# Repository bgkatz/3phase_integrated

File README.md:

# 3phase_integrated
3-phase motor controller with integrated position sensor
Firmware here:
https://os.mbed.com/users/benkatz/code/Hobbyking_Cheetah_Compact/

Firmware for new versions with DRV8323:
https://os.mbed.com/users/benkatz/code/HKC_MiniCheetah/

Documentation for using the motor drive:
https://docs.google.com/document/d/1dzNVzblz6mqB3eZVEMyi2MtSngALHdgpTaDJIW_BpS4/edit?usp=sharing

New non-mbed firmware:
https://github.com/bgkatz/motorcontrol

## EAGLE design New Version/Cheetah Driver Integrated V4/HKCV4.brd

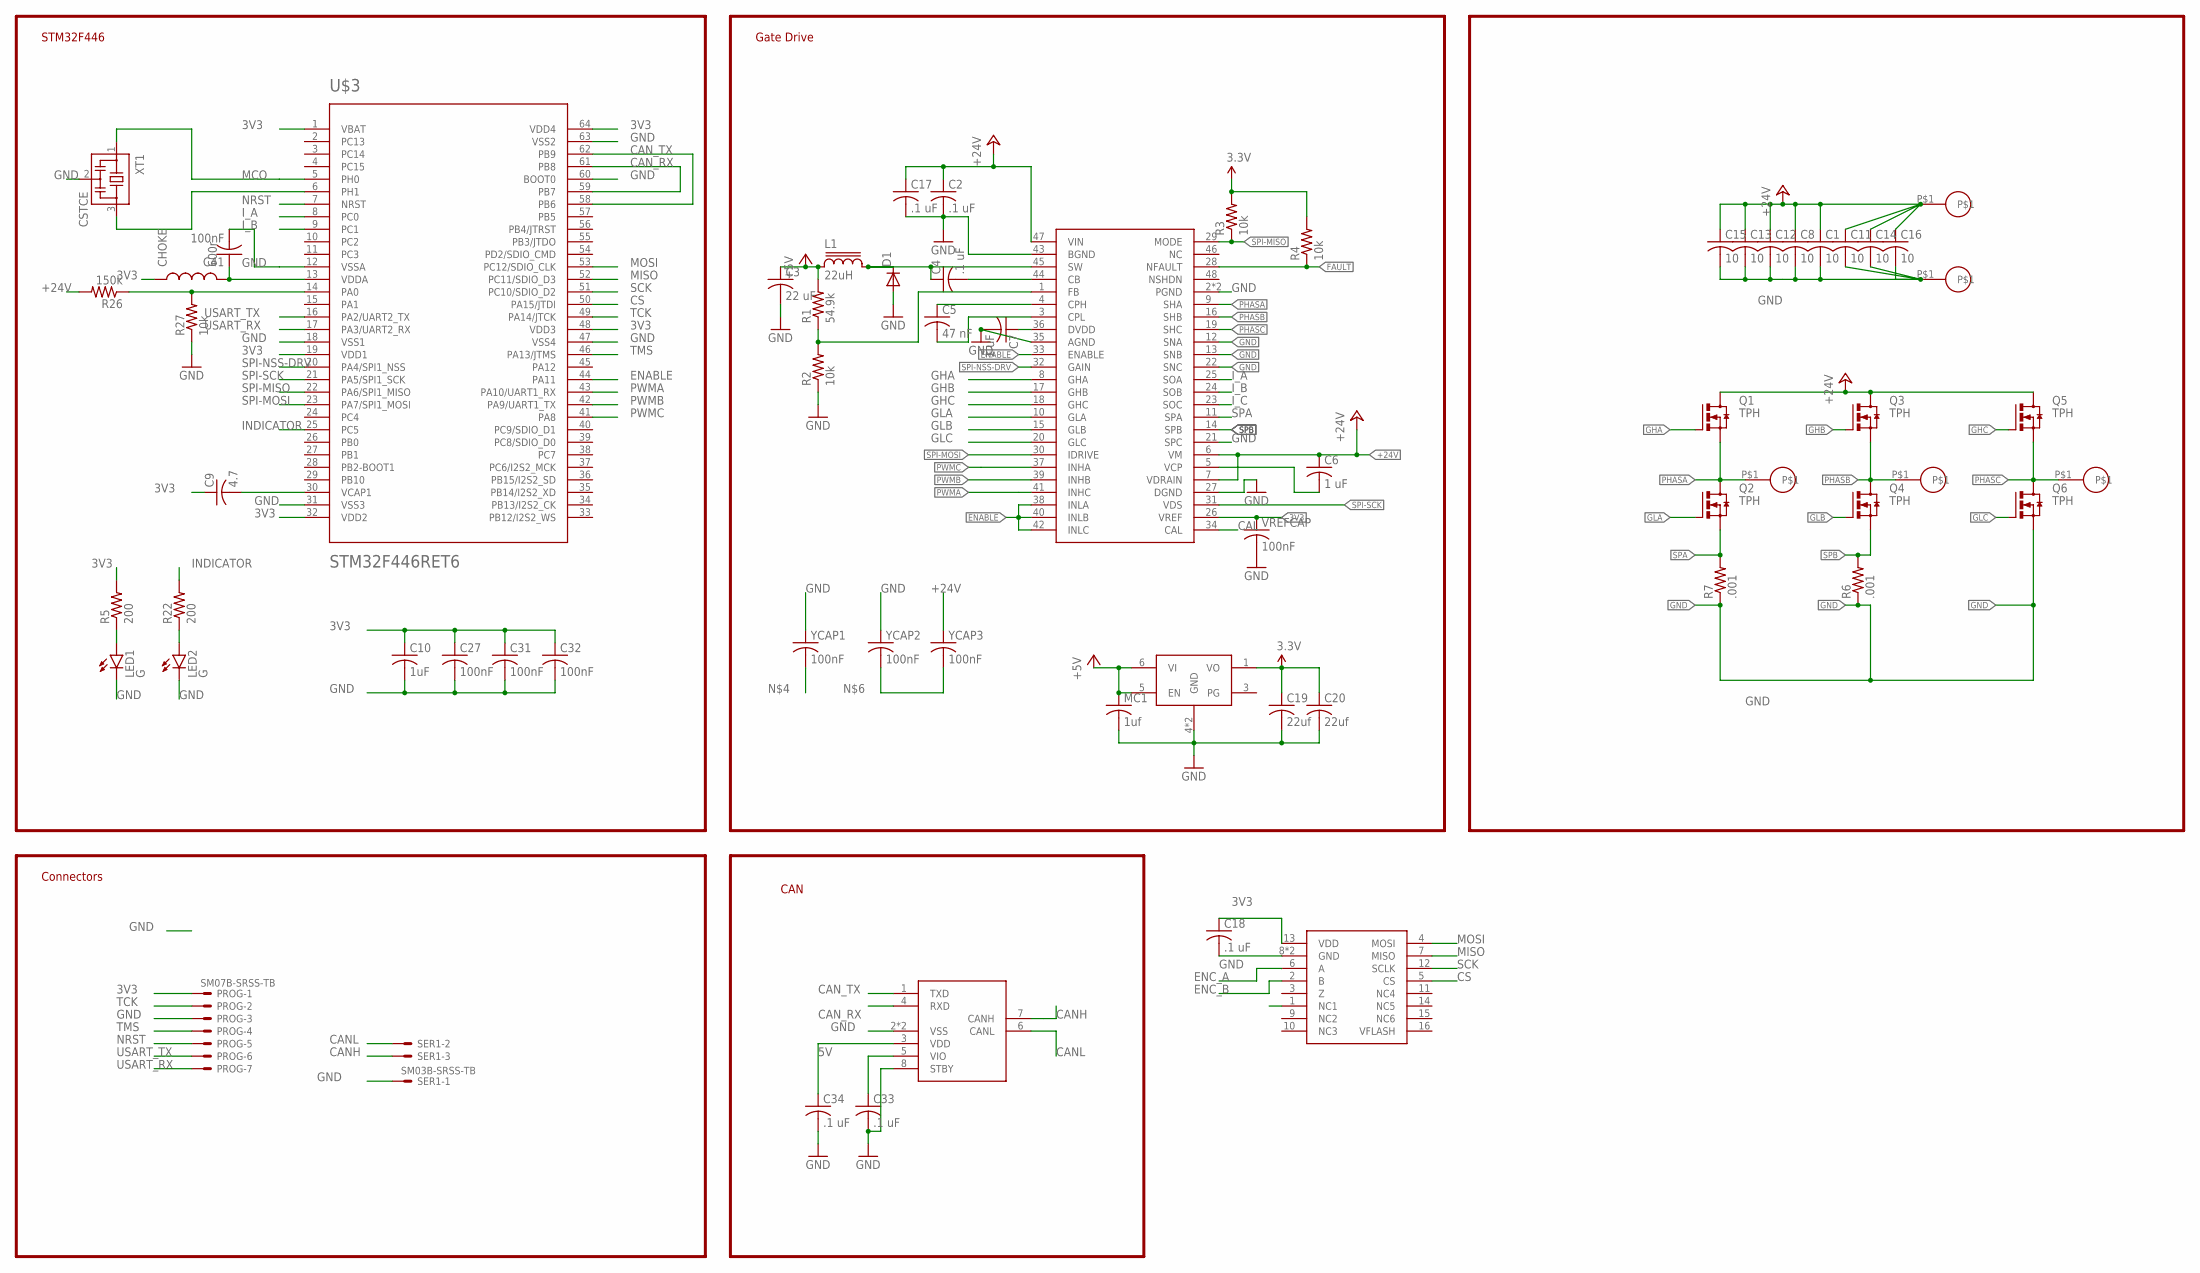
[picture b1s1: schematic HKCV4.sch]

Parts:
C1, C8, C11, C12, C13, C14, C15, C16: 10; C1206K
C2, C4: .1 uF; C0603K
C3: 22 uF; C0603K
C5: 47 nF; C0402K
C6: 1 uF; C0603K
C7: 1 uF; C0402K
C9: 4.7; C0402K
C10: 1uF; C0402K
C17: .1 uF; C1206K
C18, C33, C34: .1 uF; C0402K
C19, C20: 22uf; C0603K
C27, C31, C32: 100nF; C0402K
C41: 100nF; C0402
CHOKE: 600r; 0603
D1: DIODE-SOD123; SOD123
L1: 22uH; SDR0302
LED1, LED2: G; LED-0603
MC1: 1uf; C0402
PROG: SM07B-SRSS-TB
Q1, Q2, Q3, Q4, Q5, Q6: TPH; TRANS_TPH5900CNH,L1Q
R1: 54.9k; R0402
R2, R3, R4, R27: 10k; R0402
R5, R22: 200; R0402
R6, R7: .001; R1210
R26: 150k; R0402
SER1: SM03B-SRSS-TB
U$1: DRV8323RH; QFN50P700X700X90-49N
U$2, U$4, U$5, U$8, U$10: 18_AWG_PAD
U$3: STM32F446RET6; TQFP64
U$6: MCP2542; TDFN
U$7: LDFM; DFN6-3X3
U$11: MA700; QFN16
VREFCAP: 100nF; C0402K
XT1: CSTCE
YCAP1, YCAP2, YCAP3: 100nF; C0402K

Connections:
3V3: C9.1, C10.1, C18.1, C19.1, C20.1, C27.1, C31.1, C32.1, C33.1, CHOKE.1, PROG.1, R3.2, R4.2, R5.2, U$1.26 (VREF), U$3.1 (VBAT), U$3.19 (VDD1), U$3.32 (VDD2), U$3.48 (VDD3), U$3.64 (VDD4), U$6.5 (VIO), U$7.1 (VO), U$11.13 (VDD), VREFCAP.1
5V: C3.1, C34.1, L1.1, MC1.1, R1.2, U$6.3 (VDD), U$7.5 (EN), U$7.6 (VI)
+24V: C1.1, C2.1, C6.1, C8.1, C11.1, C12.1, C13.1, C14.1, C15.1, C16.1, C17.1, Q1.5 (D), Q1.6 (D), Q1.7 (D), Q1.8 (D), Q1.EP (D), Q3.5 (D), Q3.6 (D), Q3.7 (D), Q3.8 (D), Q3.EP (D), Q5.5 (D), Q5.6 (D), Q5.7 (D), Q5.8 (D), Q5.EP (D), R26.2, U$1.6 (VM), U$1.7 (VDRAIN), U$1.47 (VIN), U$8.P$1, YCAP3.1
BOOT: C4.2, U$1.44 (CB)
CAL: U$1.34 (CAL)
CANH: SER1.3, U$6.7 (CANH)
CANL: SER1.2, U$6.6 (CANL)
CAN_RX: U$3.59 (PB7), U$3.61 (PB8), U$6.4 (RXD)
CAN_TX: U$3.58 (PB6), U$3.62 (PB9), U$6.1 (TXD)
CPH: C5.1, U$1.4 (CPH)
CPL: C5.2, U$1.3 (CPL)
CS: U$3.50 (PA15/JTDI), U$11.5 (CS)
DEVICE3.3: C7.1, U$1.36 (DVDD)
ENABLE: U$1.33 (ENABLE), U$1.38 (INLA), U$1.40 (INLB), U$1.42 (INLC), U$3.44 (PA11)
ENC_A: U$11.6 (A)
ENC_B: U$11.2 (B)
FAULT: R4.1, U$1.28 (NFAULT)
FB: R1.1, R2.2, U$1.1 (FB)
GHA: Q1.4 (G), U$1.8 (GHA)
GHB: Q3.4 (G), U$1.17 (GHB)
GHC: Q5.4 (G), U$1.18 (GHC)
GLA: Q2.4 (G), U$1.10 (GLA)
GLB: Q4.4 (G), U$1.15 (GLB)
GLC: Q6.4 (G), U$1.20 (GLC)
GND: C1.2, C2.2, C3.2, C7.2, C8.2, C10.2, C11.2, C12.2, C13.2, C14.2, C15.2, C16.2, C17.2, C18.2, C19.2, C20.2, C27.2, C31.2, C32.2, C33.2, C34.2, C41.2, D1.A, LED1.C, LED2.C, MC1.2, PROG.3, Q6.1 (S), Q6.2 (S), Q6.3 (S), R2.1, R6.1, R7.1, R27.1, SER1.1, U$1.2 (PGND), U$1.12 (SNA), U$1.13 (SNB), U$1.21 (SPC), U$1.22 (SNC), U$1.27 (DGND), U$1.35 (AGND), U$1.43 (BGND), U$1.49 (PGND), U$3.12 (VSSA), U$3.18 (VSS1), U$3.31 (VSS3), U$3.47 (VSS4), U$3.60 (BOOT0), U$3.63 (VSS2), U$6.2 (VSS), U$6.8 (STBY), U$6.9 (VSS), U$7.4 (GND), U$7.EXP (GND), U$10.P$1, U$11.8 (GND), U$11.TH (GND), VREFCAP.2, XT1.2, YCAP1.1, YCAP2.1
INDICATOR: R22.2, U$3.25 (PC5)
I_A: U$1.25 (SOA), U$3.8 (PC0)
I_B: U$1.24 (SOB), U$3.9 (PC1)
I_C: U$1.23 (SOC)
MCO: U$3.5 (PH0), XT1.1
MISO: U$3.52 (PC11/SDIO_D3), U$11.7 (MISO)
MOSI: U$3.53 (PC12/SDIO_CLK), U$11.4 (MOSI)
unnamed: LED1.A, R5.1
unnamed: C41.1, CHOKE.2, U$3.13 (VDDA)
unnamed: C9.2, U$3.30 (VCAP1)
unnamed: YCAP2.2, YCAP3.2
unnamed: R26.1, R27.2, U$3.14 (PA0)
unnamed: LED2.A, R22.1
unnamed: U$3.6 (PH1), XT1.3
NRST: PROG.5, U$3.7 (NRST)
PHASA: Q1.1 (S), Q1.2 (S), Q1.3 (S), Q2.5 (D), Q2.6 (D), Q2.7 (D), Q2.8 (D), Q2.EP (D), U$1.9 (SHA), U$4.P$1
PHASB: Q3.1 (S), Q3.2 (S), Q3.3 (S), Q4.5 (D), Q4.6 (D), Q4.7 (D), Q4.8 (D), Q4.EP (D), U$1.16 (SHB), U$2.P$1
PHASC: Q5.1 (S), Q5.2 (S), Q5.3 (S), Q6.5 (D), Q6.6 (D), Q6.7 (D), Q6.8 (D), Q6.EP (D), U$1.19 (SHC), U$5.P$1
PWMA: U$1.41 (INHC), U$3.43 (PA10/UART1_RX)
PWMB: U$1.39 (INHB), U$3.42 (PA9/UART1_TX)
PWMC: U$1.37 (INHA), U$3.41 (PA8)
SCK: U$3.51 (PC10/SDIO_D2), U$11.12 (SCLK)
SPA: Q2.1 (S), Q2.2 (S), Q2.3 (S), R7.2, U$1.11 (SPA)
SPB: Q4.1 (S), Q4.2 (S), Q4.3 (S), R6.2, U$1.14 (SPB)
SPI-MISO: R3.1, U$1.29 (MODE), U$3.22 (PA6/SPI1_MISO)
SPI-MOSI: U$1.30 (IDRIVE), U$3.23 (PA7/SPI1_MOSI)
SPI-NSS-DRV: U$1.32 (GAIN), U$3.20 (PA4/SPI1_NSS)
SPI-SCK: U$1.31 (VDS), U$3.21 (PA5/SPI1_SCK)
SW: C4.1, D1.C, L1.2, U$1.45 (SW)
TCK: PROG.2, U$3.49 (PA14/JTCK)
TMS: PROG.4, U$3.46 (PA13/JTMS)
USART_RX: PROG.7, U$3.17 (PA3/UART2_RX)
USART_TX: PROG.6, U$3.16 (PA2/UART2_TX)
VCP: C6.2, U$1.5 (VCP)

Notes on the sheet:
Gate Drive
STM32F446
CAN
Connectors

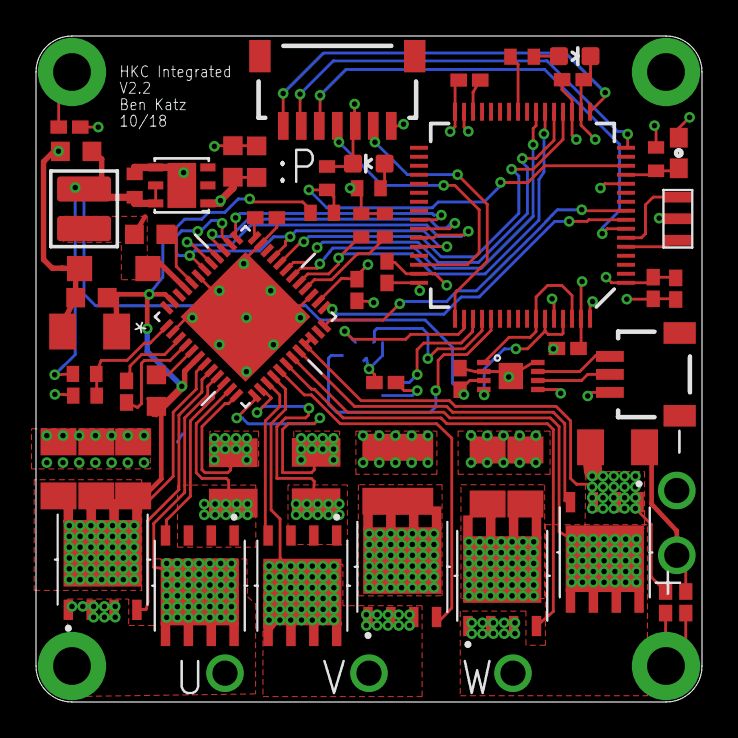
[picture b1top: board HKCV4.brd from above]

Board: 4 copper layers, 37.0 x 37.0 mm, 65 parts (1 on the bottom side), 55 nets.

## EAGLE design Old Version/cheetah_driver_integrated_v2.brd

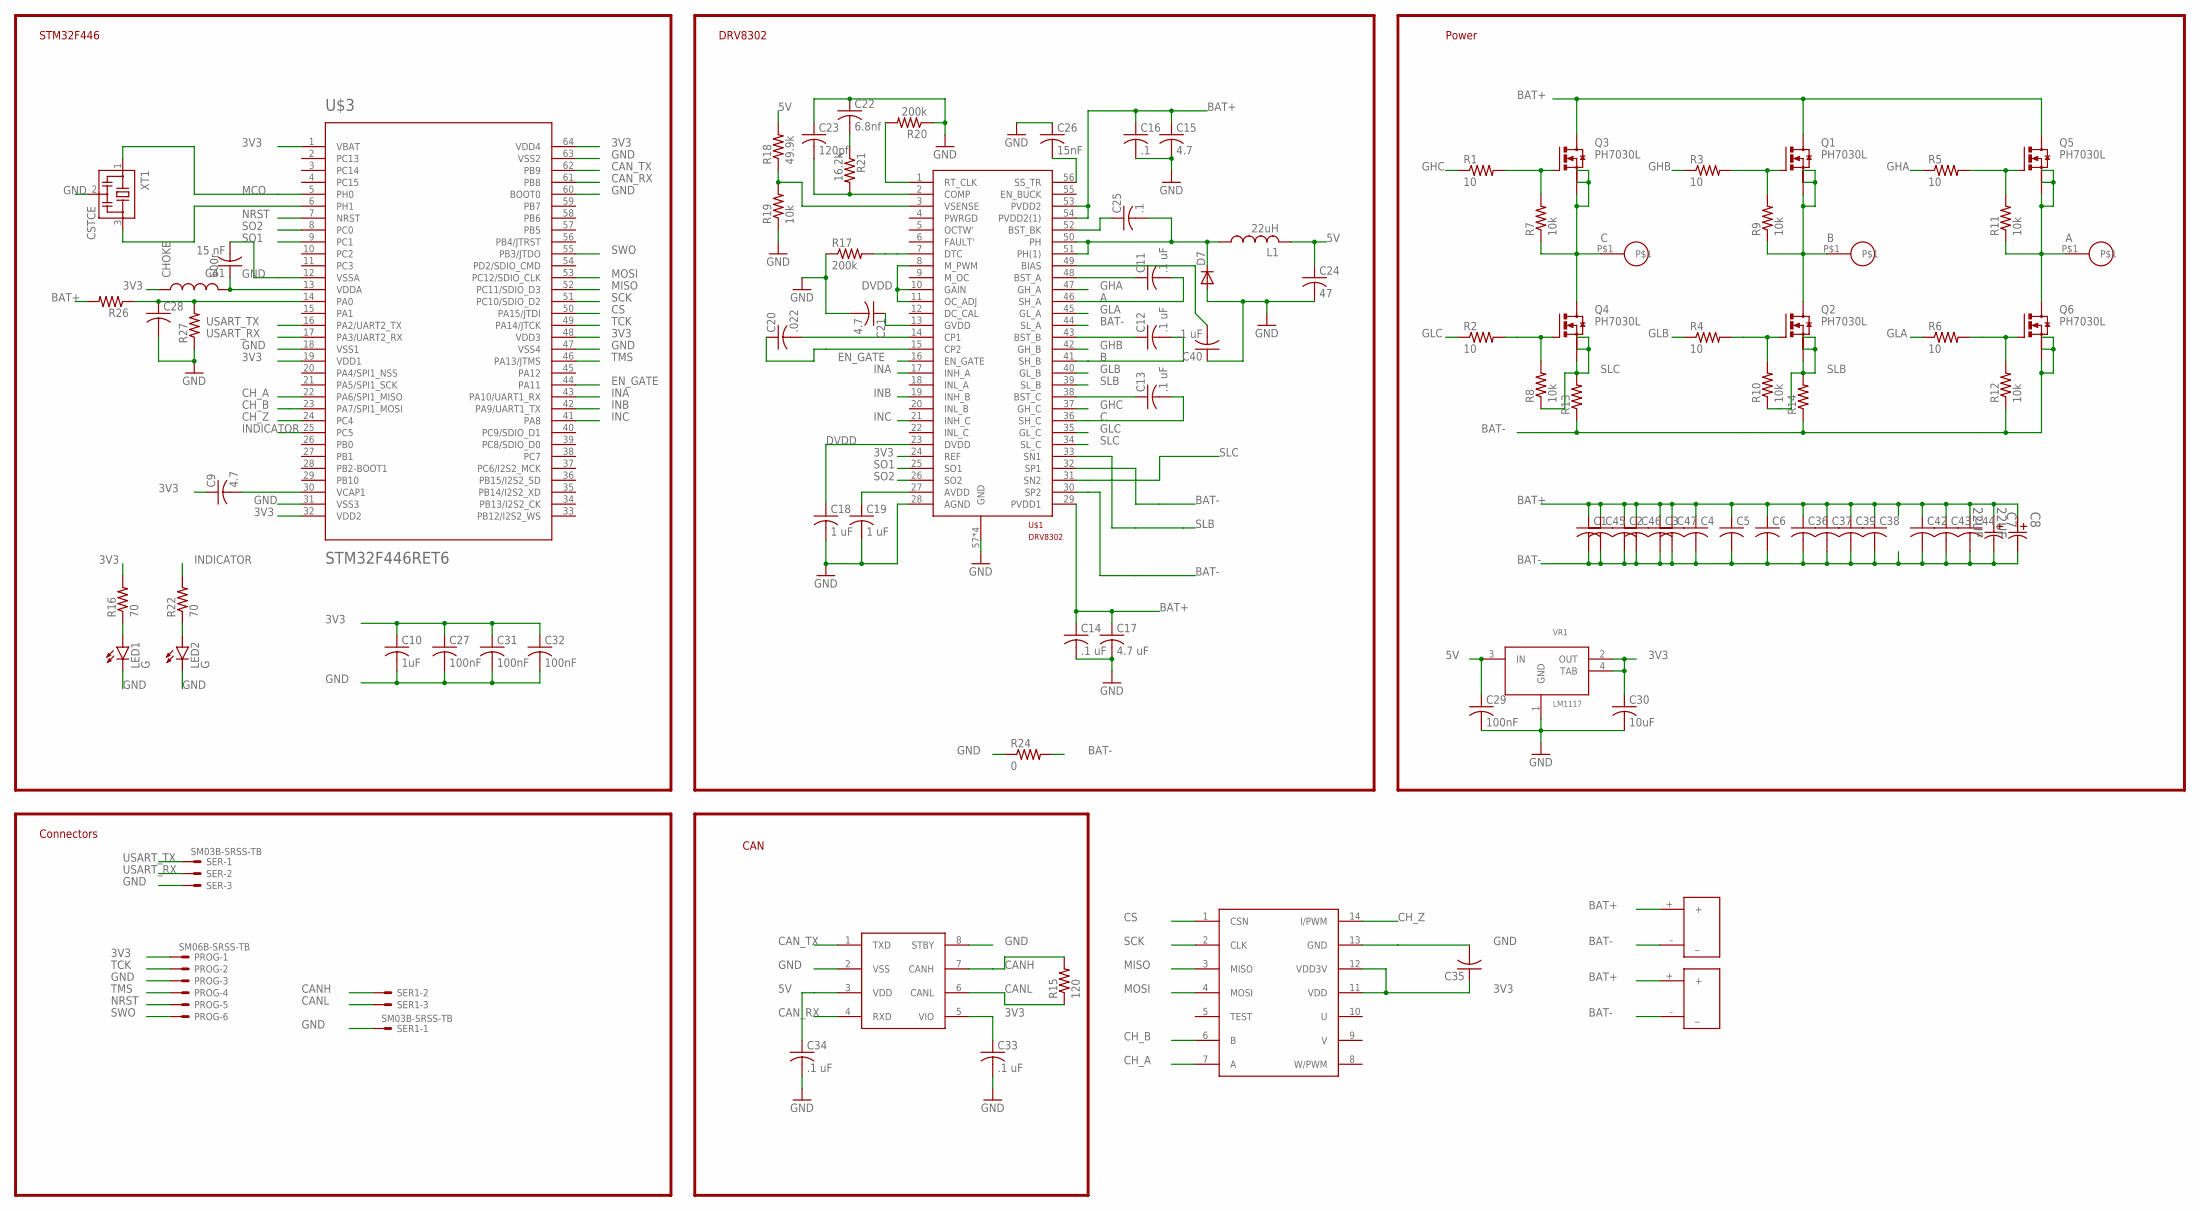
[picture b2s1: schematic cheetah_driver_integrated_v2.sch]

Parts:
C1, C2, C3, C4, C5, C6, C36, C37, C38, C39, C42, C43, C44, C45, C46, C47: C-USC1206; C1206
C7, C8: 22UF; CAPAE660X610N
C9: 4.7; C0603
C10: 1uF; C0603
C11, C12, C13, C14, C40: .1 uF; C0603
C15, C21: 4.7; C0805
C16, C25: .1; C0603
C17: 4.7 uF; C0805
C18, C19: 1 uF; C0603
C20: .022; C0603
C22: 6.8nf; C0603
C23: 120pf; C0603
C24: 47; C1210
C26: 15nF; C0603
C27, C29, C31, C32: 100nF; C0603
C28, C35: C-USC0603; C0603
C30: 10uF; C0805K
C33, C34: .1 uF; C0603K
C41: 15 nF; C0603
CHOKE: 600r; 0603
D7: DIODE-DO-214AC; DO-214AC
L1: 22uH; L4532P
LED1, LED2: G; LED-0603
PROG: SM06B-SRSS-TB
Q1, Q2, Q3, Q4, Q5, Q6: PH7030L; SOT669
R1, R2, R3, R4, R5, R6: 10; R0603
R7, R8, R9, R10, R11, R12, R19: 10k; R0603
R13, R14: R-US_R1210; R1210
R15: 120; R0603
R16, R22: 70; R0603
R17, R20: 200k; R0603
R18: 49.9k; R0603
R21: 16.2k; R0603
R24: 0; R0603
R26, R27: R-US_R0603; R0603
SER, SER1: SM03B-SRSS-TB
U$1: DRV8302; HTSSOP56
U$2, U$4, U$5: 18_AWG_PAD
U$3: STM32F446RET6; TQFP64
U$6: MCP2561; SO08
U$7: AS5147P; TSSOP14
U$8, U$9: DC_CONNECTOR; XT30_HORIZONTAL
VR1: LM1117; SOT-223
XT1: CSTCE

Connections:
3V3: C9.1, C10.1, C27.1, C30.1, C31.1, C32.1, C33.1, C35.1, CHOKE.1, PROG.1, R16.2, U$1.24 (REF), U$3.1 (VBAT), U$3.19 (VDD1), U$3.32 (VDD2), U$3.48 (VDD3), U$3.64 (VDD4), U$6.5 (VIO), U$7.11 (VDD), U$7.12 (VDD3V), VR1.2 (OUT), VR1.4 (TAB)
5V: C24.1, C29.1, C34.1, L1.2, R18.2, U$6.3 (VDD), VR1.3 (IN)
A: C11.2, Q5.1 (S), Q5.2 (S), Q5.3 (S), Q6.MB (D), R11.1, U$1.46 (SH_A), U$5.P$1
B: C12.2, Q1.1 (S), Q1.2 (S), Q1.3 (S), Q2.MB (D), R9.1, U$1.41 (SH_B), U$4.P$1
BAT+: C1.1, C2.1, C3.1, C4.1, C5.1, C6.1, C7.1, C8.1, C14.1, C15.1, C16.1, C17.1, C36.1, C37.1, C38.1, C39.1, C42.1, C43.1, C44.1, C45.1, C46.1, C47.1, Q1.MB (D), Q3.MB (D), Q5.MB (D), R26.2, U$1.29 (PVDD1), U$1.53 (PVDD2), U$1.54 (PVDD2(1)), U$8.+, U$9.+
BAT-: C1.2, C2.2, C3.2, C4.2, C5.2, C6.2, C7.2, C8.2, C36.2, C37.2, C38.2, C39.2, C42.2, C43.2, C44.2, C45.2, C46.2, C47.2, Q6.1 (S), Q6.2 (S), Q6.3 (S), R12.1, R13.1, R14.1, R24.2, U$1.30 (SP2), U$1.32 (SP1), U$1.44 (SL_A), U$8.- (_), U$9.- (_)
C: C13.2, Q3.1 (S), Q3.2 (S), Q3.3 (S), Q4.MB (D), R7.1, U$1.36 (SH_C), U$2.P$1
CANH: R15.2, SER1.2, U$6.7 (CANH)
CANL: R15.1, SER1.3, U$6.6 (CANL)
CAN_RX: U$3.61 (PB8), U$6.4 (RXD)
CAN_TX: U$3.62 (PB9), U$6.1 (TXD)
CH_A: U$3.22 (PA6/SPI1_MISO), U$7.7 (A)
CH_B: U$3.23 (PA7/SPI1_MOSI), U$7.6 (B)
CH_Z: U$3.24 (PC4), U$7.14 (I/PWM)
CS: U$3.50 (PA15/JTDI), U$7.1 (CSN)
DVDD: C18.1, U$1.8 (M_PWM), U$1.10 (GAIN), U$1.11 (OC_ADJ), U$1.23 (DVDD)
EN_GATE: U$1.16 (EN_GATE), U$3.44 (PA11)
GHA: R5.1, U$1.47 (GH_A)
GHB: R3.1, U$1.42 (GH_B)
GHC: R1.1, U$1.37 (GH_C)
GLA: R6.1, U$1.45 (GL_A)
GLB: R4.1, U$1.40 (GL_B)
GLC: R2.1, U$1.35 (GL_C)
GND: C10.2, C14.2, C15.2, C16.2, C17.2, C18.2, C19.2, C21.2, C22.1, C23.1, C24.2, C26.1, C27.2, C28.2, C29.2, C30.2, C31.2, C32.2, C33.2, C34.2, C35.2, C40.1, C41.2, D7.A, LED1.C, LED2.C, PROG.3, R17.1, R19.1, R20.1, R24.1, R27.1, SER.3, SER1.1, U$1.28 (AGND), U$1.57 (GND), U$1.P$1 (GND), U$1.P$2 (GND), U$1.P$3 (GND), U$3.12 (VSSA), U$3.18 (VSS1), U$3.31 (VSS3), U$3.47 (VSS4), U$3.60 (BOOT0), U$3.63 (VSS2), U$6.2 (VSS), U$6.8 (STBY), U$7.13 (GND), VR1.1 (GND), XT1.2
INA: U$1.17 (INH_A), U$3.43 (PA10/UART1_RX)
INB: U$1.19 (INH_B), U$3.42 (PA9/UART1_TX)
INC: U$1.21 (INH_C), U$3.41 (PA8)
INDICATOR: R22.2, U$3.25 (PC5)
MCO: U$3.5 (PH0), XT1.1
MISO: U$3.52 (PC11/SDIO_D3), U$7.3 (MISO)
MOSI: U$3.53 (PC12/SDIO_CLK), U$7.4 (MOSI)
unnamed: Q3.4 (G), R1.2, R7.2
unnamed: C41.1, CHOKE.2, U$3.13 (VDDA)
unnamed: C9.2, U$3.30 (VCAP1)
unnamed: C11.1, U$1.48 (BST_A)
unnamed: C40.2, U$1.49 (BIAS)
unnamed: C13.1, U$1.38 (BST_C)
unnamed: Q4.4 (G), R2.2, R8.2
unnamed: Q1.4 (G), R3.2, R9.2
unnamed: C12.1, U$1.43 (BST_B)
unnamed: Q5.4 (G), R5.2, R11.2
unnamed: Q6.4 (G), R6.2, R12.2
unnamed: R18.1, R19.2, U$1.3 (VSENSE)
unnamed: R17.2, U$1.7 (DTC)
unnamed: C19.1, U$1.27 (AVDD)
unnamed: C20.2, U$1.14 (CP1)
unnamed: C20.1, U$1.15 (CP2)
unnamed: C21.1, U$1.13 (GVDD)
unnamed: C23.2, R21.2, U$1.2 (COMP)
unnamed: R20.2, U$1.1 (RT_CLK)
unnamed: C22.2, R21.1
unnamed: C25.2, D7.C, L1.1, U$1.50 (PH), U$1.51 (PH(1))
unnamed: C25.1, U$1.52 (BST_BK)
unnamed: C26.2, U$1.56 (SS_TR)
unnamed: C28.1, R26.1, R27.2, U$3.14 (PA0)
unnamed: LED1.A, R16.1
unnamed: Q2.4 (G), R4.2, R10.2
unnamed: LED2.A, R22.1
unnamed: U$3.6 (PH1), XT1.3
NRST: PROG.5, U$3.7 (NRST)
SCK: U$3.51 (PC10/SDIO_D2), U$7.2 (CLK)
SLB: Q2.1 (S), Q2.2 (S), Q2.3 (S), R10.1, R14.2, U$1.33 (SN1), U$1.39 (SL_B)
SLC: Q4.1 (S), Q4.2 (S), Q4.3 (S), R8.1, R13.2, U$1.31 (SN2), U$1.34 (SL_C)
SO1: U$1.25 (SO1), U$3.9 (PC1)
SO2: U$1.26 (SO2), U$3.8 (PC0)
SWO: PROG.6, U$3.55 (PB3/JTDO)
TCK: PROG.2, U$3.49 (PA14/JTCK)
TMS: PROG.4, U$3.46 (PA13/JTMS)
USART_RX: SER.2, U$3.17 (PA3/UART2_RX)
USART_TX: SER.1, U$3.16 (PA2/UART2_TX)

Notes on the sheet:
DRV8302
STM32F446
Connectors
Power
CAN

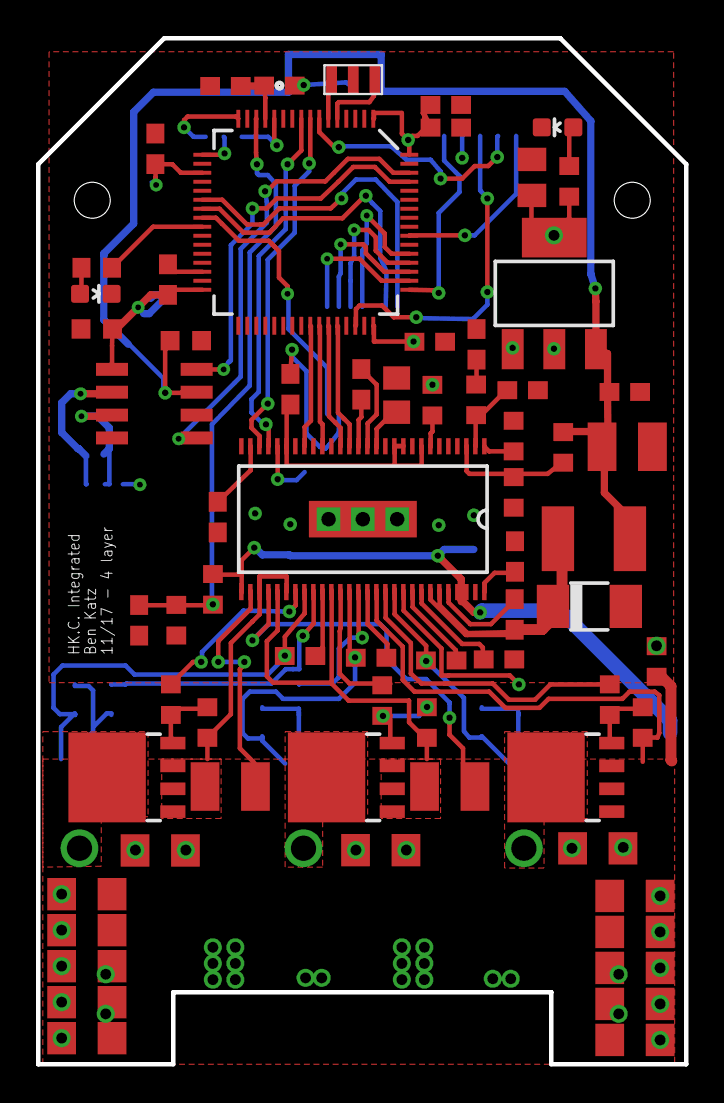
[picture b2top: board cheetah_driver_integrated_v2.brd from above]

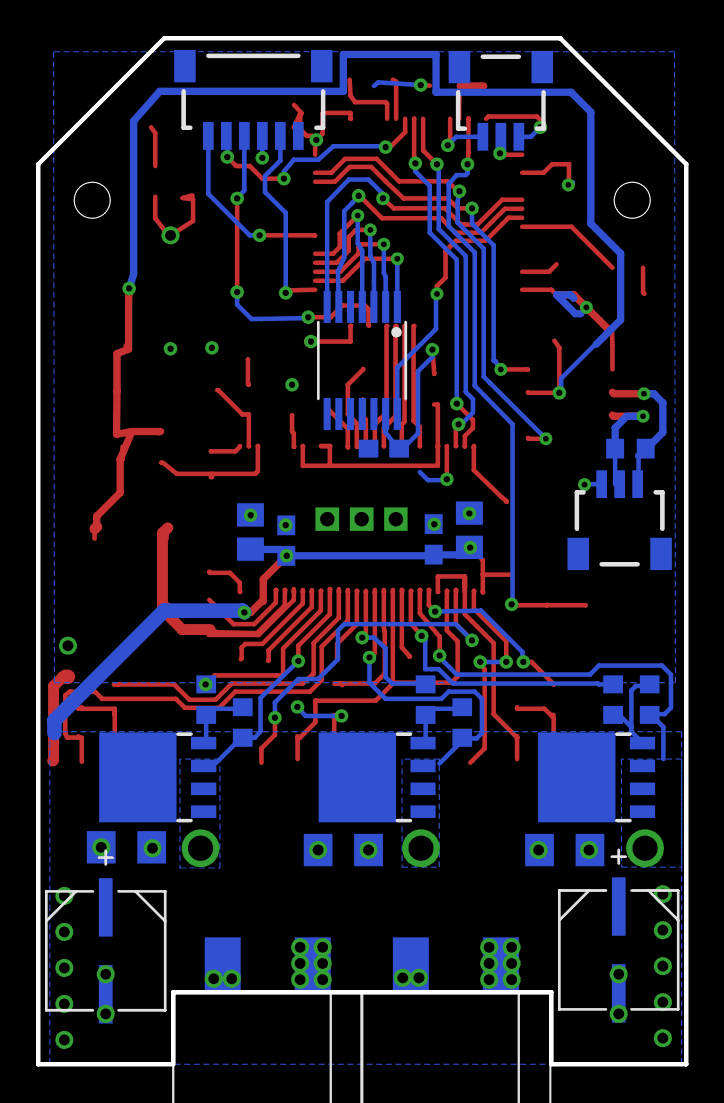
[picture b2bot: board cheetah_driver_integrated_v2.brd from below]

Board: 4 copper layers, 36.0 x 57.0 mm, 97 parts (26 on the bottom side), 70 nets.

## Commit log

2018-04-27 committing everything
2019-03-04 Added new version with drv8323
2019-04-18 updated can connector to harwin high-reliability latching
2020-10-07 Create LICENSE
2021-02-04 added build files straight from pcbway

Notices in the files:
parts and their libraries:
SparkFun-Aesthetics: Licensing: Creative Commons ShareAlike 4.0 International - https://creativecommons.org/licenses/by-sa/4.0
inductor-bourns: Copyright (C) 2008, Bob Starr
